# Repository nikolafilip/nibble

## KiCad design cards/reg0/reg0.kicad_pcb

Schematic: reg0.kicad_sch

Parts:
C1: 100n; C_Disc_D5.0mm_W2.5mm_P2.50mm
C2: 10u; CP_Radial_D5.0mm_P2.00mm
D1, D2, D3: LED; LED_D3.0mm
H1, H2: M3; MountingHole_3.2mm_M3_Pad
J1: BUS; IDC-Header_2x32_P2.54mm_Vertical
Q1, Q2, Q3, Q4, Q5, Q6, Q7, Q8, Q9, Q10, Q11, Q12, Q13, Q14, Q15, Q16, Q17, Q18, Q19, Q20, Q21, Q22, Q23, Q24, Q25, Q26, Q27, Q28, Q29, Q30, Q31, Q32, Q33, Q34, Q35, Q36, Q37, Q38, Q39, Q40, Q41, Q42, Q43, Q44, Q45, Q46, Q47, Q48, Q49, Q50, Q51, Q52, Q53, Q54, Q55, Q56, Q57, Q58, Q59, Q60, Q61, Q62, Q63, Q64, Q65, Q66, Q67, Q68, Q69, Q70, Q71, Q72, Q73, Q74, Q75, Q76, Q77, Q78, Q79, Q80, Q81, Q82, Q83, Q84, Q85, Q86, Q87, Q88, Q89, Q90, Q91, Q92, Q93, Q94, Q95, Q96, Q97, Q98, Q99: 2N7000; TO-92_Inline_Wide
R1, R4, R5, R6, R7, R8, R9, R10, R11, R12, R13, R14, R15, R16, R17, R19, R20, R21, R22, R23, R24, R25, R26, R27, R28, R29, R30, R31, R32, R34, R35, R36, R37, R38, R39, R40, R41, R42, R43, R44, R45, R46, R47, R48, R49, R50, R51: 47k; R_Axial_DIN0207_L6.3mm_D2.5mm_P5.08mm_Vertical
R2, R3: 10k; R_Axial_DIN0207_L6.3mm_D2.5mm_P5.08mm_Vertical
R18, R33: 22k; R_Axial_DIN0207_L6.3mm_D2.5mm_P5.08mm_Vertical
R52, R53, R54: 1k; R_Axial_DIN0207_L6.3mm_D2.5mm_P5.08mm_Vertical

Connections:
+5V: C1.1, C2.1, J1.1, J1.2, J1.64, R1.2, R2.2, R3.2, R4.2, R5.2, R6.2, R7.1, R8.1, R9.1, R10.1, R11.1, R12.1, R13.2, R14.2, R15.2, R16.2, R17.2, R18.2, R19.1, R20.1, R21.1, R22.1, R23.1, R24.2, R25.2, R26.2, R27.2, R28.2, R29.2, R30.1, R31.1, R32.1, R33.1, R34.1, R35.1, R36.2, R37.2, R38.2, R39.2, R40.2, R41.2, R42.1, R43.1, R44.1, R45.1, R46.1, R47.1, R48.2, R49.2, R50.2, R51.2, R52.2, R53.1, R54.1
A0: J1.14, Q14.2 (G), Q32.3 (D), Q34.2 (G), Q41.2 (G), Q91.2 (G), Q98.2 (G), R18.1
A0_dn: Q18.3 (D), Q22.2 (G), R10.2
A0_m1: Q19.3 (D), Q23.2 (G), R11.2
A0_m2: Q21.3 (D), Q26.2 (G), R12.2
A0_mq: Q23.3 (D), Q25.2 (G), Q27.2 (G), Q28.2 (G), R13.1
A0_mqi: Q27.3 (D), Q31.2 (G), R15.1
A0_mqn: Q24.2 (G), Q25.3 (D), R14.1
A0_qn: Q33.2 (G), Q34.3 (D), R19.2
A0_sa: Q28.3 (D), Q32.2 (G), R16.1
A0_sb: Q30.3 (D), Q35.2 (G), R17.1
AB: J1.45, Q8.2 (G), Q11.2 (G)
AI: J1.42, Q7.2 (G), Q9.2 (G)
AO: J1.41, Q90.2 (G)
AON0: Q90.3 (D), Q94.2 (G), R49.1
B0: J1.18, Q12.2 (G), Q43.2 (G), Q61.3 (D), Q63.2 (G), Q93.2 (G), Q99.2 (G), R33.2
B0_dn: Q47.3 (D), Q51.2 (G), R25.1
B0_m1: Q48.3 (D), Q52.2 (G), R26.1
B0_m2: Q50.3 (D), Q55.2 (G), R27.1
B0_mq: Q52.3 (D), Q54.2 (G), Q56.2 (G), Q57.2 (G), R28.1
B0_mqi: Q56.3 (D), Q60.2 (G), R30.2
B0_mqn: Q53.2 (G), Q54.3 (D), R29.1
B0_qn: Q62.2 (G), Q63.3 (D), R34.2
B0_sa: Q57.3 (D), Q61.2 (G), R31.2
B0_sb: Q59.3 (D), Q64.2 (G), R32.2
BA: J1.46, Q37.2 (G), Q40.2 (G)
BD0: Q94.3 (D), Q96.2 (G), R51.1
BI: J1.44, Q36.2 (G), Q38.2 (G)
BO: J1.43, Q92.2 (G)
BON0: Q92.3 (D), Q95.2 (G), R50.1
BUS0#: J1.10, Q6.2 (G), Q96.3 (D)
CLK: J1.6, Q1.2 (G), Q2.2 (G)
CLKN: Q1.3 (D), Q4.2 (G), R1.1
D0: Q6.3 (D), Q10.2 (G), Q39.2 (G), Q67.2 (G), R4.1
DA0: Q15.3 (D), Q18.2 (G), Q19.2 (G), R9.2
DA0_1: Q9.3 (D), Q15.2 (G), R6.1
DA0_2: Q11.3 (D), Q16.2 (G), R7.2
DA0_3: Q13.3 (D), Q17.2 (G), R8.2
DB0: Q44.3 (D), Q47.2 (G), Q48.2 (G), R24.1
DB0_1: Q38.3 (D), Q44.2 (G), R21.2
DB0_2: Q40.3 (D), Q45.2 (G), R22.2
DB0_3: Q42.3 (D), Q46.2 (G), R23.2
DO0: Q70.3 (D), Q72.2 (G), Q73.2 (G), R38.1
DO0_1: Q66.3 (D), Q70.2 (G), R36.1
DO0_2: Q68.3 (D), Q71.2 (G), R37.1
GND: C1.2, C2.2, J1.3, J1.4, J1.5, J1.7, J1.63, Q1.1 (S), Q2.1 (S), Q3.1 (S), Q4.1 (S), Q5.1 (S), Q6.1 (S), Q7.1 (S), Q8.1 (S), Q10.1 (S), Q12.1 (S), Q14.1 (S), Q17.1 (S), Q18.1 (S), Q20.1 (S), Q22.1 (S), Q24.1 (S), Q26.1 (S), Q27.1 (S), Q29.1 (S), Q31.1 (S), Q33.1 (S), Q35.1 (S), Q36.1 (S), Q37.1 (S), Q39.1 (S), Q41.1 (S), Q43.1 (S), Q46.1 (S), Q47.1 (S), Q49.1 (S), Q51.1 (S), Q53.1 (S), Q55.1 (S), Q56.1 (S), Q58.1 (S), Q60.1 (S), Q62.1 (S), Q64.1 (S), Q65.1 (S), Q67.1 (S), Q69.1 (S), Q71.1 (S), Q72.1 (S), Q74.1 (S), Q76.1 (S), Q78.1 (S), Q80.1 (S), Q81.1 (S), Q83.1 (S), Q85.1 (S), Q87.1 (S), Q89.1 (S), Q91.1 (S), Q93.1 (S), Q95.1 (S), Q96.1 (S), Q97.1 (S), Q98.1 (S), Q99.1 (S)
HOLDA: Q7.3 (D), Q8.3 (D), Q13.2 (G), R5.1
HOLDB: Q36.3 (D), Q37.3 (D), Q42.2 (G), R20.2
unnamed: D1.2 (A), R52.1
unnamed: D1.1 (K), Q97.3 (D)
unnamed: D2.2 (A), R53.2
unnamed: D2.1 (K), Q98.3 (D)
unnamed: D3.2 (A), R54.2
unnamed: D3.1 (K), Q99.3 (D)
unnamed: Q9.1 (S), Q10.3 (D)
unnamed: Q11.1 (S), Q12.3 (D)
unnamed: Q13.1 (S), Q14.3 (D)
unnamed: Q15.1 (S), Q16.3 (D)
unnamed: Q16.1 (S), Q17.3 (D)
unnamed: Q19.1 (S), Q20.3 (D)
unnamed: Q21.1 (S), Q22.3 (D)
unnamed: Q23.1 (S), Q24.3 (D)
unnamed: Q25.1 (S), Q26.3 (D)
unnamed: Q28.1 (S), Q29.3 (D)
unnamed: Q30.1 (S), Q31.3 (D)
unnamed: Q32.1 (S), Q33.3 (D)
unnamed: Q34.1 (S), Q35.3 (D)
unnamed: Q38.1 (S), Q39.3 (D)
unnamed: Q40.1 (S), Q41.3 (D)
unnamed: Q42.1 (S), Q43.3 (D)
unnamed: Q44.1 (S), Q45.3 (D)
unnamed: Q45.1 (S), Q46.3 (D)
unnamed: Q48.1 (S), Q49.3 (D)
unnamed: Q50.1 (S), Q51.3 (D)
unnamed: Q52.1 (S), Q53.3 (D)
unnamed: Q54.1 (S), Q55.3 (D)
unnamed: Q57.1 (S), Q58.3 (D)
unnamed: Q59.1 (S), Q60.3 (D)
unnamed: Q61.1 (S), Q62.3 (D)
unnamed: Q63.1 (S), Q64.3 (D)
unnamed: Q66.1 (S), Q67.3 (D)
unnamed: Q68.1 (S), Q69.3 (D)
unnamed: Q70.1 (S), Q71.3 (D)
unnamed: Q73.1 (S), Q74.3 (D)
unnamed: Q75.1 (S), Q76.3 (D)
unnamed: Q77.1 (S), Q78.3 (D)
unnamed: Q79.1 (S), Q80.3 (D)
unnamed: Q82.1 (S), Q83.3 (D)
unnamed: Q84.1 (S), Q85.3 (D)
unnamed: Q86.1 (S), Q87.3 (D)
unnamed: Q88.1 (S), Q89.3 (D)
unnamed: Q90.1 (S), Q91.3 (D)
unnamed: Q92.1 (S), Q93.3 (D)
unnamed: Q94.1 (S), Q95.3 (D)
OI: J1.48, Q65.2 (G), Q66.2 (G)
OIN: Q65.3 (D), Q68.2 (G), R35.2
OUT0: Q69.2 (G), Q86.3 (D), Q88.2 (G), Q97.2 (G), R47.2
OUT0_dn: Q72.3 (D), Q76.2 (G), R39.1
OUT0_m1: Q73.3 (D), Q77.2 (G), R40.1
OUT0_m2: Q75.3 (D), Q80.2 (G), R41.1
OUT0_mq: Q77.3 (D), Q79.2 (G), Q81.2 (G), Q82.2 (G), R42.2
OUT0_mqi: Q81.3 (D), Q85.2 (G), R44.2
OUT0_mqn: Q78.2 (G), Q79.3 (D), R43.2
OUT0_qn: Q87.2 (G), Q88.3 (D), R48.1
OUT0_sa: Q82.3 (D), Q86.2 (G), R45.2
OUT0_sb: Q84.3 (D), Q89.2 (G), R46.2
PH1: Q2.3 (D), Q3.3 (D), Q5.2 (G), Q20.2 (G), Q21.2 (G), Q49.2 (G), Q50.2 (G), Q74.2 (G), Q75.2 (G), R2.1
PH2: Q3.2 (G), Q4.3 (D), Q5.3 (D), Q29.2 (G), Q30.2 (G), Q58.2 (G), Q59.2 (G), Q83.2 (G), Q84.2 (G), R3.1

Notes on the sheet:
NIBBLE CARD REG0 - REGISTER BIT 0: bit 0 of A, B and OUT
Cell: 2N7000 + 47k pull-up (NMOS, see docs/gate-cell.md). 99 transistors, 54 resistors, 3 LEDs, 100 x 100 mm (docs/cards.md). From the bus header: BUS0# (data, active low), CLK, and the control lines AI AO BI BO BA AB OI (docs/isa.md). To the bus header: A0 and B0 (for the ALU and the panel); BUS0#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
TWO-PHASE CLOCK (one per card): PH1 = NOR(CLK, PH2) opens the masters while CLK is low, PH2 = NOR(CLKN, PH1) opens the slaves while CLK is high. The cross-coupling means a phase cannot start rising until the other is fully low, so a flip-flop is never transparent.
BUS INPUT: D = NOT BUS# (the bus is active low)
REGISTER A INPUT MUX: DA = AI.D + AB.B + HOLDA.A, HOLDA = NOR(AI, AB). NAND-NAND form: three 2-input NANDs into a 3-input NAND
REGISTER A: master-slave D flip-flop, 22k pull-up on Q (A feeds the ALU, the panel, both muxes and the bus driver)
REGISTER B INPUT MUX: DB = BI.D + BA.A + HOLDB.B
REGISTER B
OUT REGISTER INPUT MUX: DO = OI.D + OIN.OUT
OUT REGISTER (the display)
BUS DRIVER: pull BUS# low when AO.A or BO.B
INDICATORS: OUT, A, B
LED_OUT0
LED_A0
LED_B0
Decoupling
Mounting holes

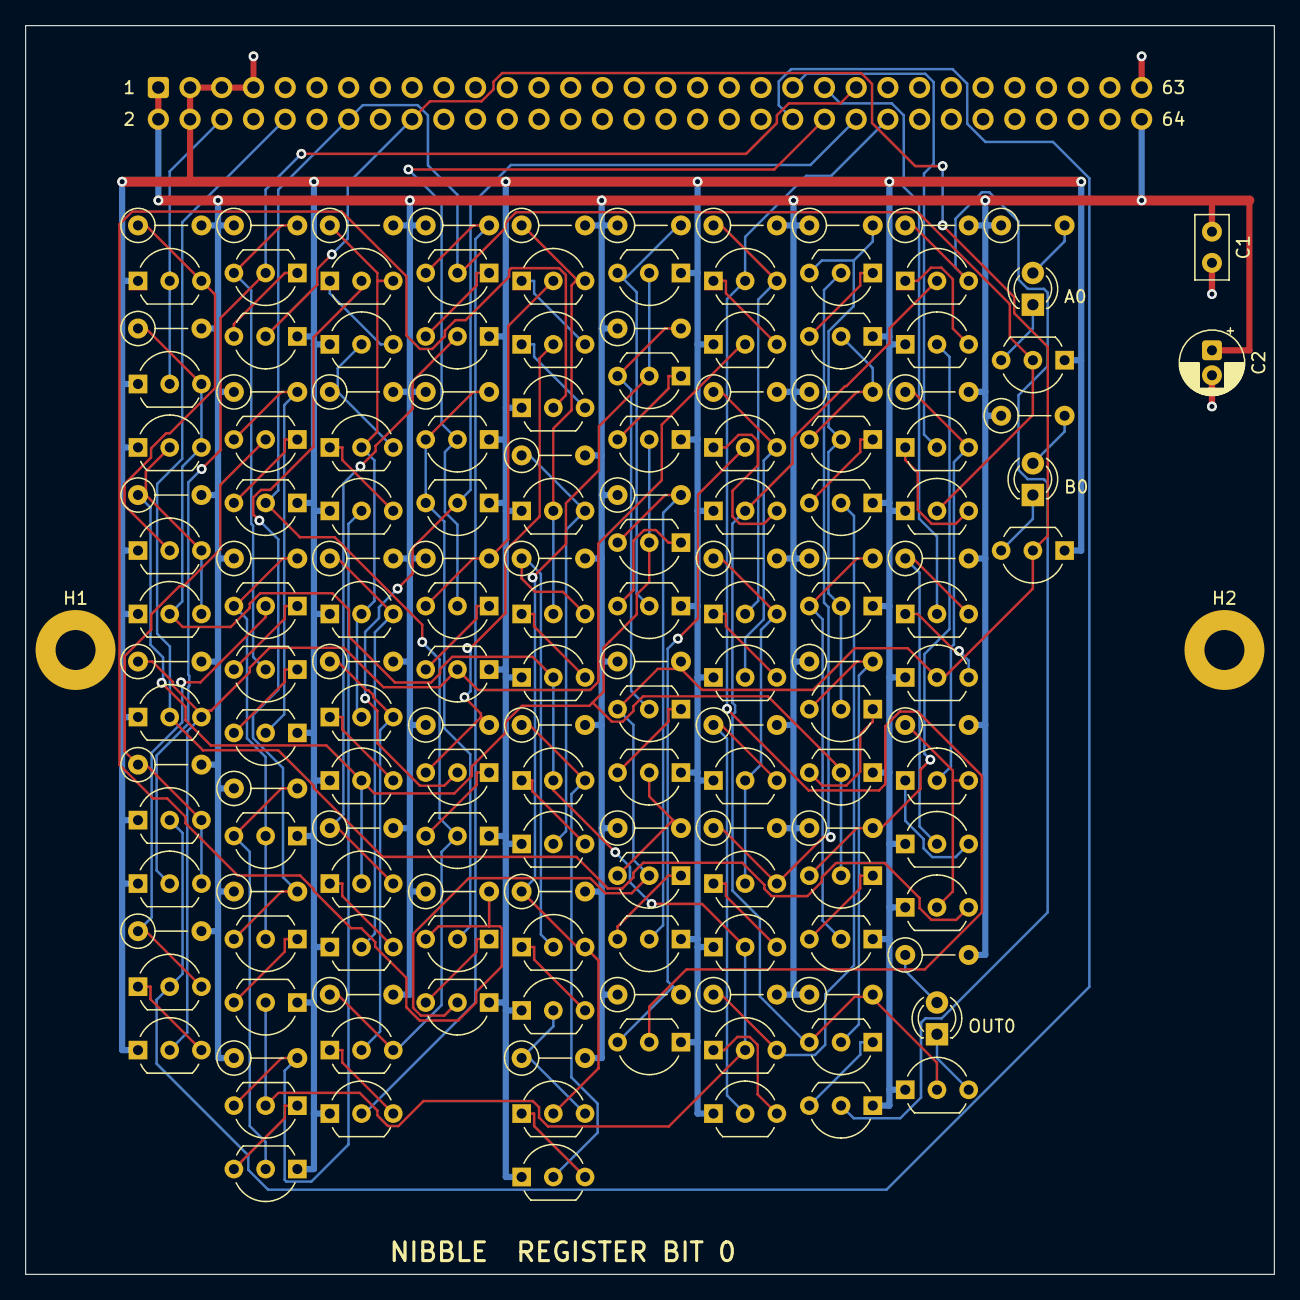
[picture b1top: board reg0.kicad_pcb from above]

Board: 2 copper layers, 100.0 x 100.0 mm, 161 parts (1 on the bottom side), 108 nets.

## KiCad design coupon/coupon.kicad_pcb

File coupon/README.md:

# Gate coupon

26 transistors on a small board: the cell in copper, measured before any other
board is trusted. Power on J1 (5 V), inputs on J2, scope probes on the test loops.

| Test point | What it measures |
|---|---|
| TP_RING | 5-inverter ring oscillator, buffered. Gate delay = period / 10 (simulated period 14 µs) |
| TP_FO1 | Inverter output driving 1 gate. Rise time at fan-out 1 (simulated 4 µs to 2.5 V) |
| TP_FO10 | Inverter output driving 10 gates. Rise time at fan-out 10 (simulated 28 µs) |
| TP_NAND | 3-input NAND, three transistors in series. Output low with N1=N2=N3=1 (simulated 0.9 mV) |
| TP_NOR | 3-input NOR. Output low (simulated 0.1 mV) |
| TP_BUS | Open-drain driver on IN with the hub's 10k pull-up |

Also: supply current with everything low, and the LED cell on IN.
Fill the measured column in `docs/gate-cell.md`. Generated by `sim/build_coupon.py`.

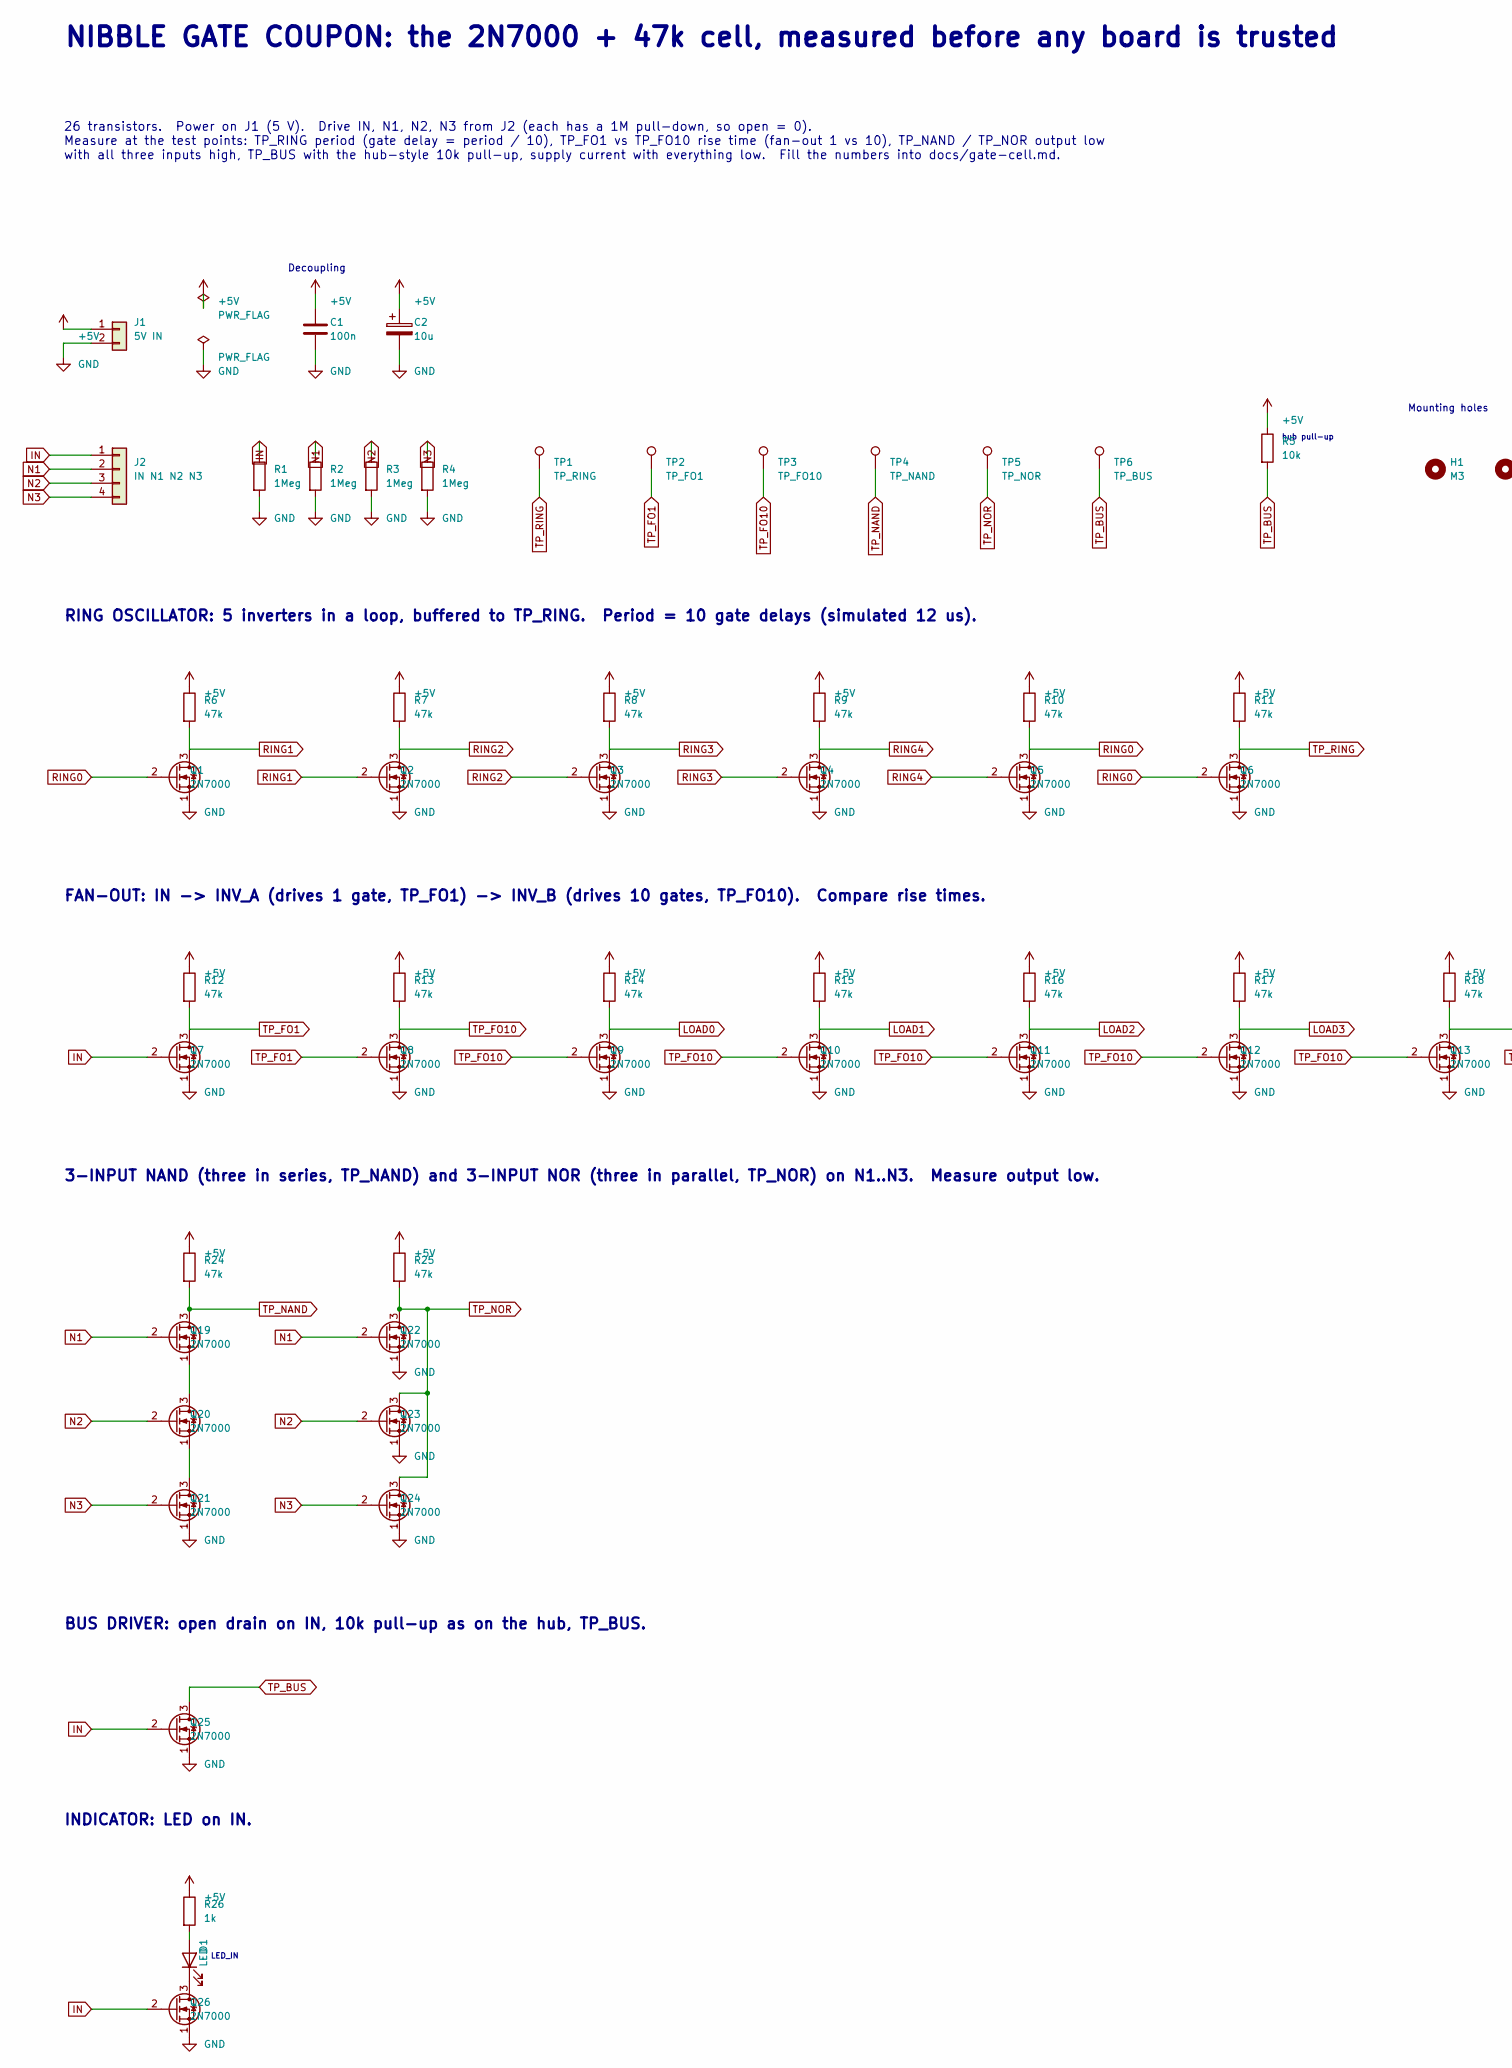
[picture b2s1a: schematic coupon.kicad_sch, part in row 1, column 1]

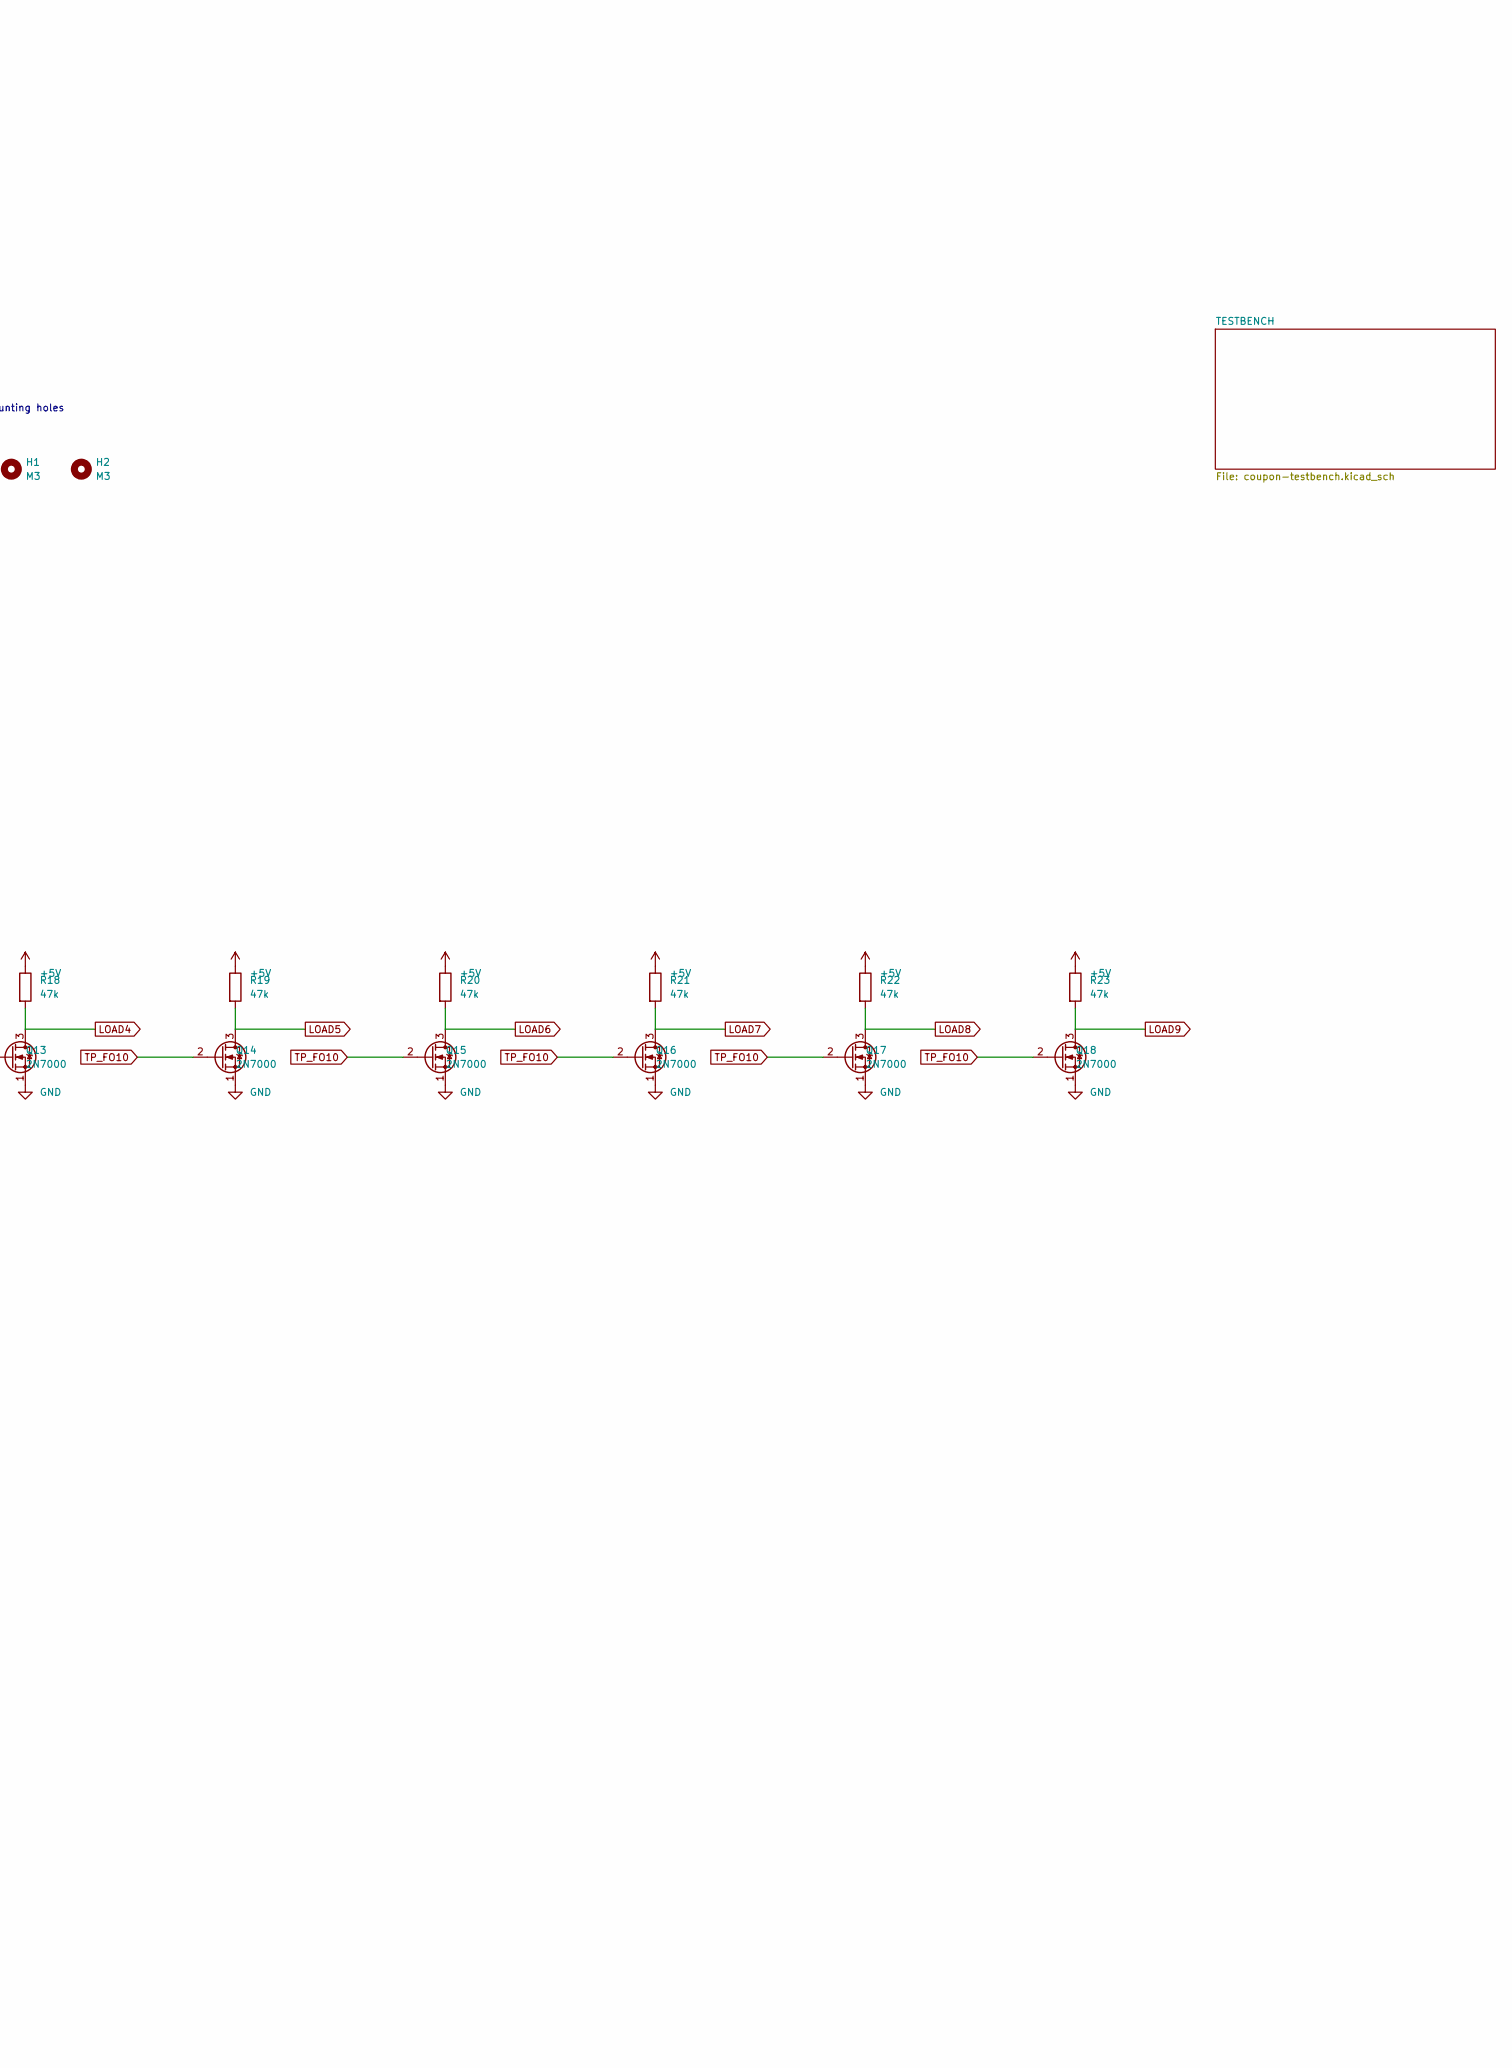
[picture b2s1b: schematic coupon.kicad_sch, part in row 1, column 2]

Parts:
C1: 100n; C_Disc_D5.0mm_W2.5mm_P2.50mm
C2: 10u; CP_Radial_D5.0mm_P2.00mm
D1: LED; LED_D3.0mm
H1, H2: M3; MountingHole_3.2mm_M3_Pad
J1: 5V IN; PinHeader_1x02_P2.54mm_Vertical
J2: IN N1 N2 N3; PinHeader_1x04_P2.54mm_Vertical
Q1, Q2, Q3, Q4, Q5, Q6, Q7, Q8, Q9, Q10, Q11, Q12, Q13, Q14, Q15, Q16, Q17, Q18, Q19, Q20, Q21, Q22, Q23, Q24, Q25, Q26: 2N7000; TO-92_Inline_Wide
R1, R2, R3, R4: 1Meg; R_Axial_DIN0207_L6.3mm_D2.5mm_P5.08mm_Vertical
R5: 10k; R_Axial_DIN0207_L6.3mm_D2.5mm_P5.08mm_Vertical
R6, R7, R8, R9, R10, R11, R12, R13, R14, R15, R16, R17, R18, R19, R20, R21, R22, R23, R24, R25: 47k; R_Axial_DIN0207_L6.3mm_D2.5mm_P5.08mm_Vertical
R26: 1k; R_Axial_DIN0207_L6.3mm_D2.5mm_P5.08mm_Vertical
TP1: TP_RING; TestPoint_Loop_D2.50mm_Drill1.0mm
TP2: TP_FO1; TestPoint_Loop_D2.50mm_Drill1.0mm
TP3: TP_FO10; TestPoint_Loop_D2.50mm_Drill1.0mm
TP4: TP_NAND; TestPoint_Loop_D2.50mm_Drill1.0mm
TP5: TP_NOR; TestPoint_Loop_D2.50mm_Drill1.0mm
TP6: TP_BUS; TestPoint_Loop_D2.50mm_Drill1.0mm

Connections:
+5V: C1.1, C2.1, J1.1, R5.1, R6.1, R7.1, R8.1, R9.1, R10.1, R11.1, R12.1, R13.1, R14.1, R15.1, R16.1, R17.1, R18.1, R19.1, R20.1, R21.1, R22.1, R23.1, R24.1, R25.1, R26.1
GND: C1.2, C2.2, J1.2, Q1.1 (S), Q2.1 (S), Q3.1 (S), Q4.1 (S), Q5.1 (S), Q6.1 (S), Q7.1 (S), Q8.1 (S), Q9.1 (S), Q10.1 (S), Q11.1 (S), Q12.1 (S), Q13.1 (S), Q14.1 (S), Q15.1 (S), Q16.1 (S), Q17.1 (S), Q18.1 (S), Q21.1 (S), Q22.1 (S), Q23.1 (S), Q24.1 (S), Q25.1 (S), Q26.1 (S), R1.2, R2.2, R3.2, R4.2
IN: J2.1, Q7.2 (G), Q25.2 (G), Q26.2 (G), R1.1
LOAD0: Q9.3 (D), R14.2
LOAD1: Q10.3 (D), R15.2
LOAD2: Q11.3 (D), R16.2
LOAD3: Q12.3 (D), R17.2
LOAD4: Q13.3 (D), R18.2
LOAD5: Q14.3 (D), R19.2
LOAD6: Q15.3 (D), R20.2
LOAD7: Q16.3 (D), R21.2
LOAD8: Q17.3 (D), R22.2
LOAD9: Q18.3 (D), R23.2
N1: J2.2, Q19.2 (G), Q22.2 (G), R2.1
N2: J2.3, Q20.2 (G), Q23.2 (G), R3.1
N3: J2.4, Q21.2 (G), Q24.2 (G), R4.1
unnamed: D1.2 (A), R26.2
unnamed: D1.1 (K), Q26.3 (D)
unnamed: Q19.1 (S), Q20.3 (D)
unnamed: Q20.1 (S), Q21.3 (D)
RING0: Q1.2 (G), Q5.3 (D), Q6.2 (G), R10.2
RING1: Q1.3 (D), Q2.2 (G), R6.2
RING2: Q2.3 (D), Q3.2 (G), R7.2
RING3: Q3.3 (D), Q4.2 (G), R8.2
RING4: Q4.3 (D), Q5.2 (G), R9.2
TP_BUS: Q25.3 (D), R5.2, TP6.1
TP_FO1: Q7.3 (D), Q8.2 (G), R12.2, TP2.1
TP_FO10: Q8.3 (D), Q9.2 (G), Q10.2 (G), Q11.2 (G), Q12.2 (G), Q13.2 (G), Q14.2 (G), Q15.2 (G), Q16.2 (G), Q17.2 (G), Q18.2 (G), R13.2, TP3.1
TP_NAND: Q19.3 (D), R24.2, TP4.1
TP_NOR: Q22.3 (D), Q23.3 (D), Q24.3 (D), R25.2, TP5.1
TP_RING: Q6.3 (D), R11.2, TP1.1

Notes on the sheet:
NIBBLE GATE COUPON: the 2N7000 + 47k cell, measured before any board is trusted
26 transistors. Power on J1 (5 V). Drive IN, N1, N2, N3 from J2 (each has a 1M pull-down, so open = 0). Measure at the test points: TP_RING period (gate delay = period / 10), TP_FO1 vs TP_FO10 rise time (fan-out 1 vs 10), TP_NAND / TP_NOR output low with all three inputs high, TP_BUS with the hub-s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
Decoupling
hub pull-up
Mounting holes
RING OSCILLATOR: 5 inverters in a loop, buffered to TP_RING. Period = 10 gate delays (simulated 12 us).
FAN-OUT: IN -> INV_A (drives 1 gate, TP_FO1) -> INV_B (drives 10 gates, TP_FO10). Compare rise times.
3-INPUT NAND (three in series, TP_NAND) and 3-INPUT NOR (three in parallel, TP_NOR) on N1..N3. Measure output low.
BUS DRIVER: open drain on IN, 10k pull-up as on the hub, TP_BUS.
INDICATOR: LED on IN.
LED_IN

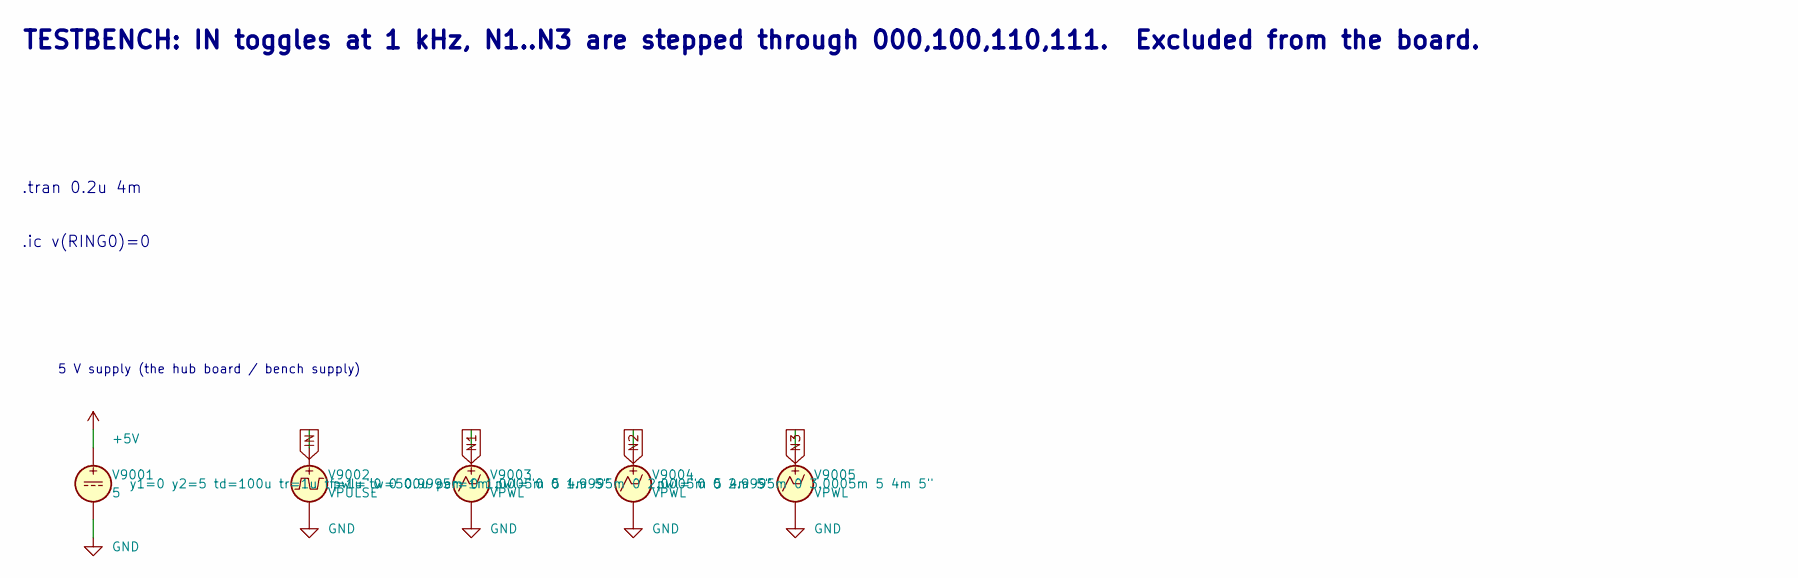
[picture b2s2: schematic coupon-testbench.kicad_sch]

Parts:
V9001: 5
V9002: VPULSE
V9003, V9004, V9005: VPWL

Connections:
unnamed: V9001.2, V9002.2, V9003.2, V9004.2, V9005.2

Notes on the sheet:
TESTBENCH: IN toggles at 1 kHz, N1..N3 are stepped through 000,100,110,111. Excluded from the board.
.tran 0.2u 4m
.ic v(RING0)=0
5 V supply (the hub board / bench supply)

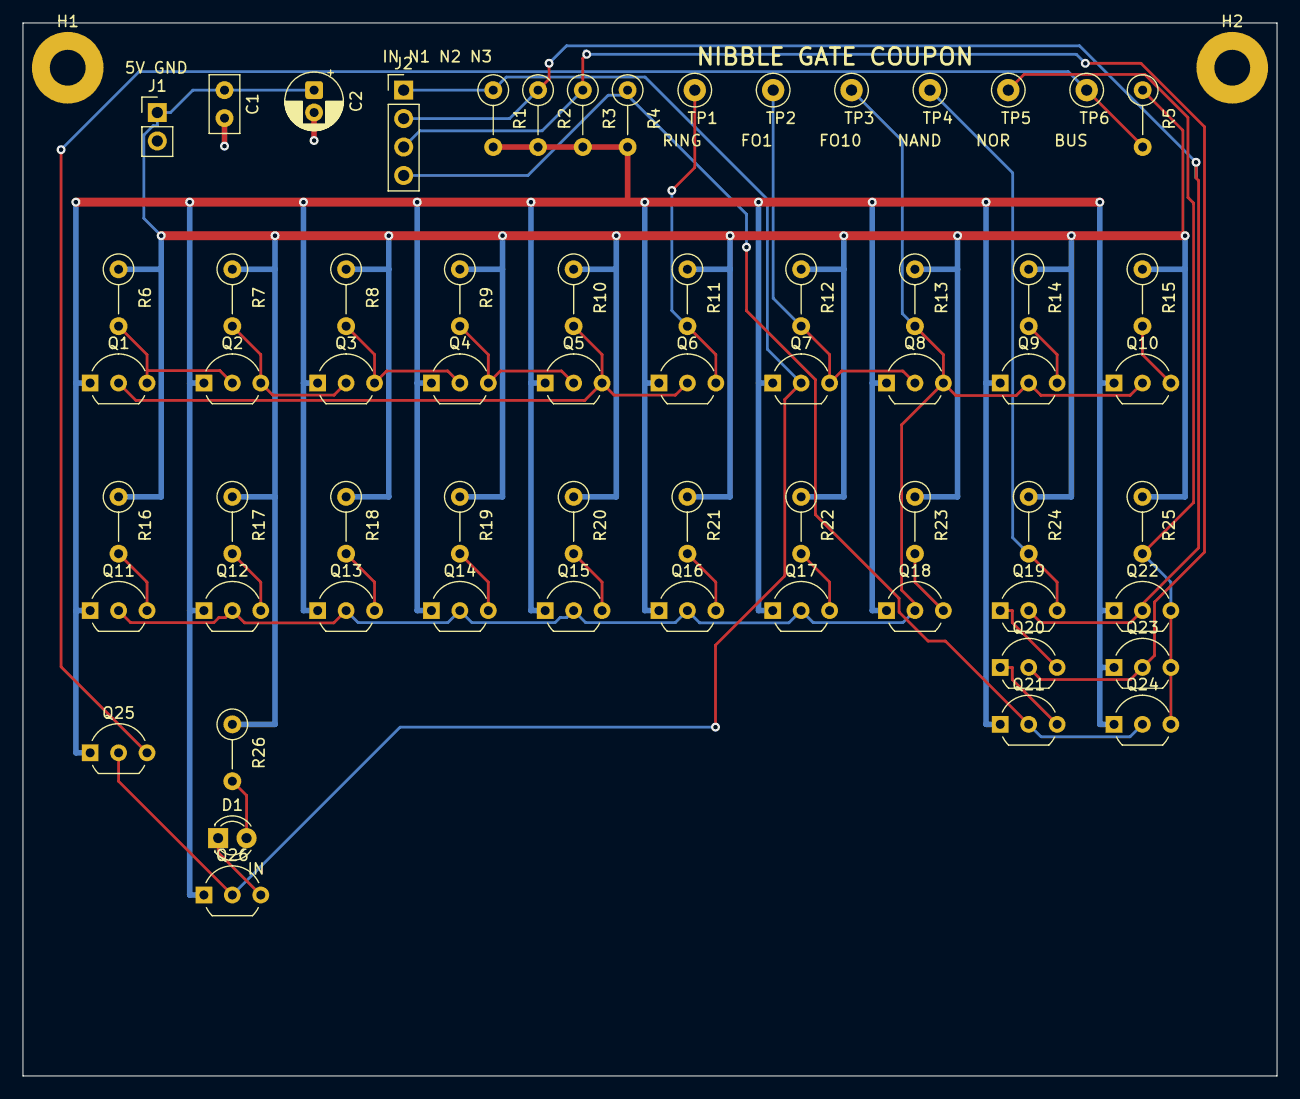
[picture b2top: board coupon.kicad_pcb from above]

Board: 2 copper layers, 112.0 x 94.0 mm, 65 parts (0 on the bottom side), 31 nets.
